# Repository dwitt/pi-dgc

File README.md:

# pi-dgc
Raspberry Pi based Digital Gauge Cluster

Setup steps on Buster Lite:
- raspi-config / Boot Options / Console Autologin
- `sudo apt-get install libgles2`
- `sudo apt-get install --no-install-recommends xserver-xorg x11-xserver-utils xinit`
- `sudo apt-get install --no-install-recommends chromium-browser`
- `sudo apt-get install unclutter`
- `sudo apt-get install default-jdk`
- Follow all steps on http://skpang.co.uk/catalog/images/raspberrypi/pican/PICAN3_UGA_10.pdf to setup/enable the PiCAN3
- Follow instructions on https://www.raspberrypi.org/forums/viewtopic.php?t=24679#p227301 to set the proper resolution
- `mkdir ~/pidgc`
- Put pidgc.jar into ~/pidgc
- Edit `/boot/config.txt`. Add:
~~~
initial_turbo=60
disable_splash=1
boot_delay=0
~~~
- Add `quiet fastboot` to `/boot/cmdline.txt`
- Add contents of `linux/network_interfaces` from repo into file `/etc/network/interfaces`
- Add contents of `linux/.xinitrc` from repo into file `~/.xinitrc`
- Add contents of `linux/.bash_profile` from repo into file `~/.bash_profile`
- Copy contents of `linux/pidgc.service` from repo into file `/etc/systemd/system/pidgc.service`
- `sudo systemctl enable pidgc.service`
- `sudo /sbin/ip link set can0 up type can bitrate 500000`
- `sudo adduser pi dialout`
- Disable unused services once everything is done. This decreases boot time substantially:
  - sudo systemctl disable ssh
  - sudo systemctl disable hciuart 
  - sudo systemctl disable nmbd # If you have samba installed
  - sudo systemctl disable smbd # If you have samba installed
  - sudo systemctl disable systemd-timesyncd
  - sudo systemctl disable wpa_supplicant
  - sudo systemctl disable rpi-eeprom-update
  - sudo systemctl disable raspi-config
  - sudo systemctl disable networking
  - sudo systemctl disable dhcpcd

Now when you reboot the system should start into startx and run Chromium with http://localhost:8080.

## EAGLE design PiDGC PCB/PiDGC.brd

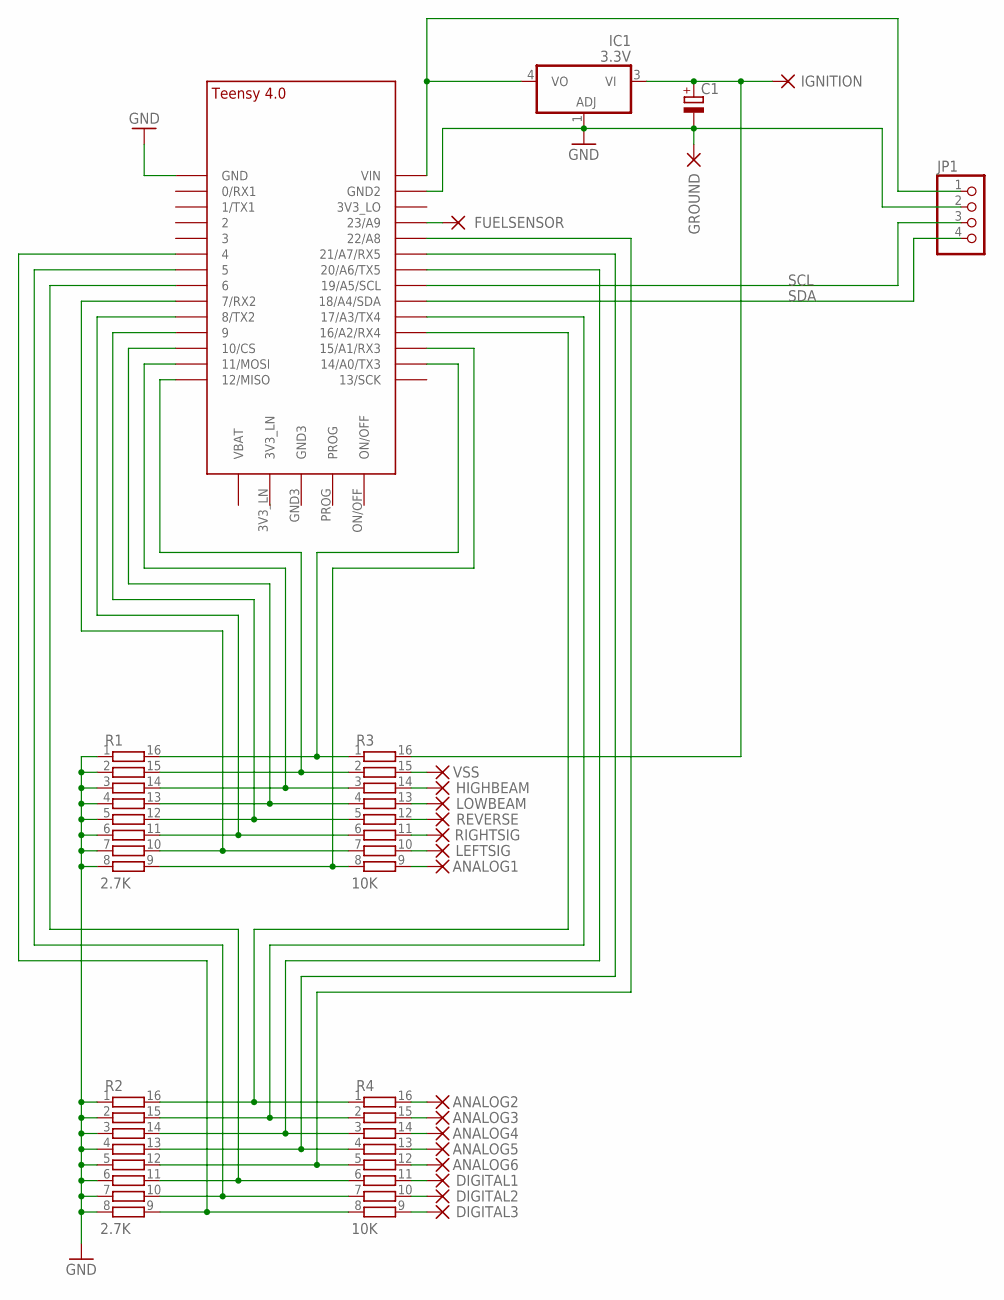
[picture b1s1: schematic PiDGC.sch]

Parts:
ANALOG1, ANALOG2, ANALOG3, ANALOG4, ANALOG5, ANALOG6: WIREPAD3,81/1,4; 3,81/1,4
C1: CPOL-EUE7.5-16; E7,5-16
DIGITAL1, DIGITAL2, DIGITAL3: WIREPAD3,81/1,4; 3,81/1,4
FUELSENSOR: WIREPAD3,81/1,4; 3,81/1,4
GROUND: WIREPAD3,81/1,4; 3,81/1,4
HIGHBEAM: WIREPAD3,81/1,4; 3,81/1,4
IC1: 3.3V; SOT223
IGNITION: WIREPAD3,81/1,4; 3,81/1,4
JP1: PINHD-1X4; 1X04
LEFTSIG: WIREPAD3,81/1,4; 3,81/1,4
LOWBEAM: WIREPAD3,81/1,4; 3,81/1,4
R1, R2: 2.7K; SO16
R3, R4: 10K; SO16
REVERSE: WIREPAD3,81/1,4; 3,81/1,4
RIGHTSIG: WIREPAD3,81/1,4; 3,81/1,4
U$1: TEENSY_4.0
VSS: WIREPAD3,81/1,4; 3,81/1,4

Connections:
GND: C1.-, GROUND.1, IC1.1 (ADJ), JP1.2, R1.1, R1.2, R1.3, R1.4, R1.5, R1.6, R1.7, R1.8, R2.1, R2.2, R2.3, R2.4, R2.5, R2.6, R2.7, R2.8, U$1.GND, U$1.GND2
unnamed: IC1.4 (VO), JP1.1, U$1.VIN
unnamed: C1.+, IC1.3 (VI), IGNITION.1, R3.16
unnamed: R1.14, R3.3, U$1.11/MOSI
unnamed: R1.13, R3.4, U$1.10/CS
unnamed: R1.12, R3.5, U$1.9/CS (9)
unnamed: R1.11, R3.6, U$1.8 (8/TX2)
unnamed: R1.10, R3.7, U$1.7 (7/RX2)
unnamed: R1.9, R3.8, U$1.15/A1 (15/A1/RX3)
unnamed: R2.16, R4.1, U$1.16/A2 (16/A2/RX4)
unnamed: R2.15, R4.2, U$1.17/A3 (17/A3/TX4)
unnamed: R2.14, R4.3, U$1.20/A6 (20/A6/TX5)
unnamed: R2.13, R4.4, U$1.21/A7 (21/A7/RX5)
unnamed: R2.12, R4.5, U$1.22/A8
unnamed: R2.11, R4.6, U$1.6
unnamed: R2.10, R4.7, U$1.5
unnamed: R2.9, R4.8, U$1.4/CANRX (4)
unnamed: R3.15, VSS.1
unnamed: HIGHBEAM.1, R3.14
unnamed: LOWBEAM.1, R3.13
unnamed: R3.12, REVERSE.1
unnamed: R3.11, RIGHTSIG.1
unnamed: LEFTSIG.1, R3.10
unnamed: ANALOG1.1, R3.9
unnamed: ANALOG2.1, R4.16
unnamed: ANALOG3.1, R4.15
unnamed: ANALOG4.1, R4.14
unnamed: ANALOG5.1, R4.13
unnamed: ANALOG6.1, R4.12
unnamed: DIGITAL1.1, R4.11
unnamed: DIGITAL2.1, R4.10
unnamed: DIGITAL3.1, R4.9
unnamed: FUELSENSOR.1, U$1.23/A9
unnamed: R1.16, R3.1, U$1.14/A0 (14/A0/TX3)
unnamed: R1.15, R3.2, U$1.12/MISO
SCL: JP1.3, U$1.19/A5/SCL
SDA: JP1.4, U$1.18/A4/SDA

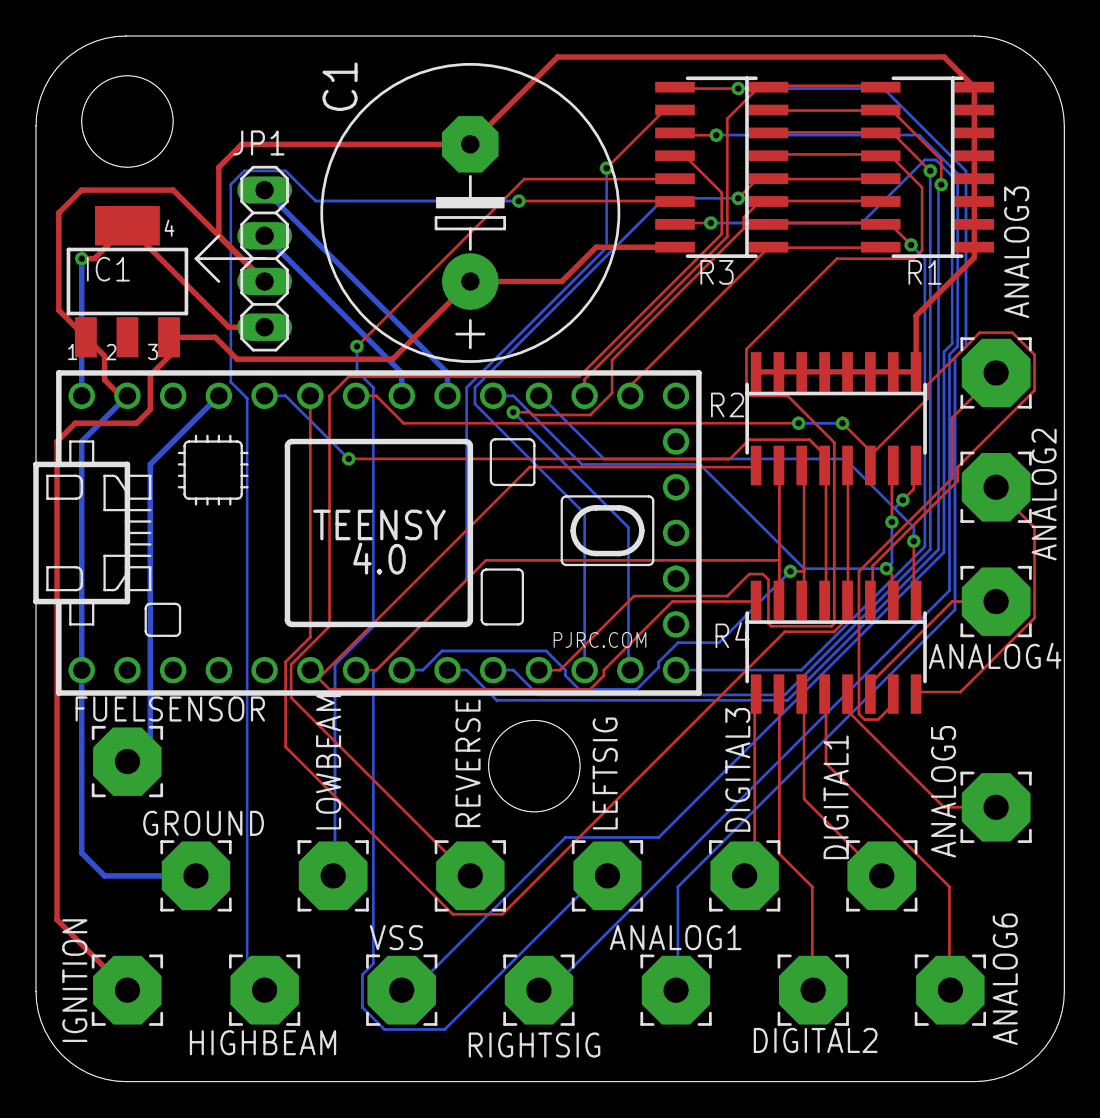
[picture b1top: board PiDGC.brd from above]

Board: 2 copper layers, 57.1 x 58.1 mm, 26 parts (0 on the bottom side), 37 nets.

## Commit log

2021-02-12 Update LICENSE
2021-02-12 Add websockets
2021-02-12 Styling updates
2021-02-12 Shift light
2021-02-13 Work
2021-02-15 More work
2021-02-21 Lots of work
2021-02-21 Remove project files
2021-02-21 Backup camera code
2021-02-22 Convert to 1920x720
2021-02-22 Revert "Convert to 1920x720"
    This reverts commit 63595c39b0dd3ec087ce2cecf5d90b94b98e0e2a.
2021-02-23 Working
2021-02-23 Faster spring startup
2021-02-24 Latest
2021-03-09 Convert to typescript
2021-03-09 Add more stuff
2021-03-13 various work
2021-03-17 Add schematic/pcb/etc.
